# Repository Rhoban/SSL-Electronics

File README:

> Copyright (C) 2019  Adrien Boussicault <adrien.boussicault@labri.fr>
>
> This program is free software: you can redistribute it and/or
> modify it under the terms of the GNU Lesser General Public
> License as published by the Free Software Foundation, either
> version 3 of the License, or (at your option) any later version.
>
> This program is distributed in the hope that it will be useful,
> but WITHOUT ANY WARRANTY; without even the implied warranty of
> MERCHANTABILITY or FITNESS FOR A PARTICULAR PURPOSE.  See the GNU
> Lesser General Public License for more details.
>
> You should have received a copy of the GNU Lesser General Public
> License along with this program.  If not, see
> <http://www.gnu.org/licenses/>.

##################
# Installation : #
##################

Install the following package :

sudo apt-get install dfu-util cu build-essential

Uninstall the modemmanager : 

sudo apt-get remove modemmanager

( The modmeManger will grab the serial line of the USB : /dev/ttyACM0;
if you are using this service, you should prefer do desactivate them with the
following command : systemctl stop ModemManager.service )

Add Udev permition to have access to /dev/ttyACMO

sudo adduser USER plugdev
sudo adduser USER dialout

Add/edit the file /etc/udev/rules.d/42-cycloide.rules and add the following 
lines :

ATTRS{idProduct}=="4567", ATTRS{idVendor}=="f123", MODE="664", GROUP="plugdev" SYMLINK+="brushless"
ATTRS{idProduct}=="5740", ATTRS{idVendor}=="0483", MODE="664", GROUP="plugdev" SYMLINK+="stm32"

The first line is for the normal mode. It allow to comunicate with the 
brushless. The second one is used to flash the firmware.

Restart the udev service :
 
sudo /etc/init.d/udev restart

Download the last ARM compilator from the website :

https://developer.arm.com/tools-and-software/open-source-software/developer-tools/gnu-toolchain/gnu-rm/downloads

And install the compilator in a chosen ARM_DIRECTORY directory.

OPTIONAL INSTALLATION :

You can install JLink tools in order to use JTAG to flash or print.
Go to the website :  

#########################################
# Compile the application               #
#########################################

Jute type

make GCC_PATH=<ARM_DIRECTORY>/bin

###################
# Flash the board #
###################

Three solution are possible dependong of the situation.
IF THE BOARD HAVE NOT YET BEEN FLASHED, YOU SHOULD USE SOLUTION 1) OR 2).
Solution 3) is the most simple one and it is used to update the firmware (we 
need the board to be yet flashed).

Short description of the 3 solutions : 
 1) FLASH BY USB USING THE RESET AND BOOT0 BUTTONS
   This solution doesn't need the board to be yet flashed.
   This solution need USB wire and and an access to the BOOT0 and RESET buttons
   of the board
 2) FLASH BY JTAG USING THE JLink SOFWTARE
   This solution doesn't need the board to be yet flashed.
   This solution need an USB wire (for the power) and a JTAG for the connection.
   This solution Use JLink software (see Optional installation)
   The JLink software download just the part of the memory that have changed.
   So the flash operation are fast and the life of the flash memory is 
   increased.
 3) FLASH BY USB WITHOUT USING THE RESET BUTTONS
   This solution need the board to be yet flashed
   ( by using 1) or  2) ).
   This solution just need a USB wire ! :)
   This solution DO NOT require an acess to the BOOT0 and RESET button ! :)

1) FLASH BY USB USING THE RESET AND BOOT0 BUTTONS

 Connect the USB wire.

 Press and hold the BOOT0 button, then press and realease de RESET button,
 and finally release the BOOT0 button.

 Type the command :
 ./first_flash_with_usb_and_reset_button.sh

2) FLASH BY JTAG USING THE JLink SOFWTARE

 ./jtag_flash.sh

3) FLASH BY USB WITHOUT THE RESET BUTTONS

 ./usb_flash.sh

########################
# Connect to the board #
########################

First Connect the USB wire.

Execute the command 

dmesg

to know on which device the board is connected (usualy it is /dev/ttyACM0).

Open a command line into the board by typing:

cu -l /dev/ttyACM0

Enjoy :) 
(In the command line, help is the first helpfull command to know)

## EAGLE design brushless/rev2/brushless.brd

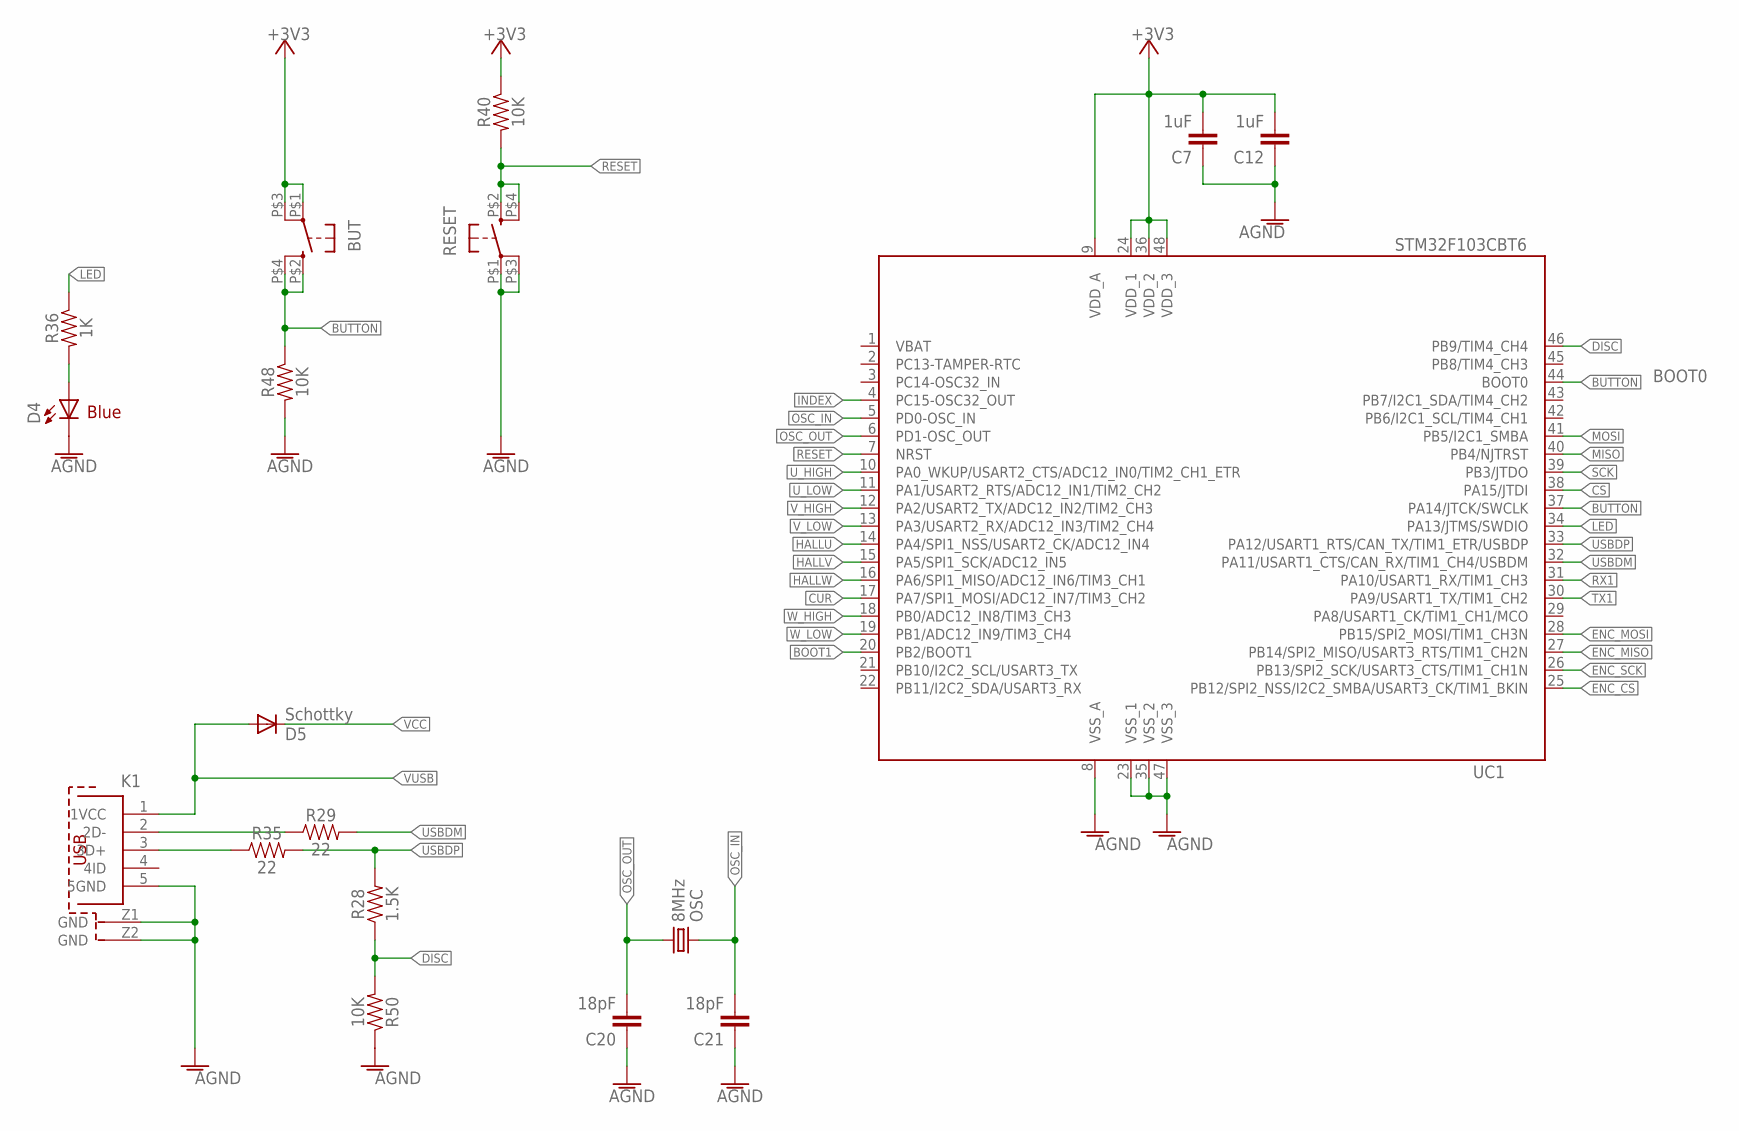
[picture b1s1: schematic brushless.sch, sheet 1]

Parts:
BUT: KMR211GLFS; PUSHBUTTON-KMR241GLFS; FARNELL 1437637
C7, C12: 1uF; 0805@1; FARNELL 2496946
C20, C21: 18pF; 0805@1; FARNELL 1414620
D4: Blue; LED-1206; FARNELL 1581233
D5: Schottky; SOD-323; FARNELL 8734593
K1: 614105150721; FARNELL 2470821
OSC: 8MHz; CRYSTAL-SMD-5X3; FARNELL 2467818
R28: 1.5K; 0805; FARNELL 2446909
R29, R35: 22; 0805; FARNELL 2446926
R36: 1K; 0805; FARNELL 2446904
R40, R48, R50: 10K; 0805; FARNELL 2447553
RESET: KMR211GLFS; PUSHBUTTON-KMR241GLFS; FARNELL 1437637
UC1: STM32F103CBT6; STM32_LQFP48; FARNELL 1606327

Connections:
+3V3: BUT.P$1 (1), BUT.P$3 (3), C7.2, C12.2, R40.1, UC1.9 (VDD_A), UC1.24 (VDD_1), UC1.36 (VDD_2), UC1.48 (VDD_3); also elsewhere on the board
AGND: C7.1, C12.1, C20.1, C21.1, D4.C, K1.5 (5GND), K1.Z1 (GND), K1.Z2 (GND), R48.2, R50.1, RESET.P$1 (1), RESET.P$3 (3), UC1.8 (VSS_A), UC1.23 (VSS_1), UC1.35 (VSS_2), UC1.47 (VSS_3); also elsewhere on the board
BOOT1: UC1.20 (PB2/BOOT1)
BUTTON: BUT.P$2 (2), BUT.P$4 (4), R48.1, UC1.37 (PA14/JTCK/SWCLK), UC1.44 (BOOT0)
CS: UC1.38 (PA15/JTDI); also elsewhere on the board
CUR: UC1.17 (PA7/SPI1_MOSI/ADC12_IN7/TIM3_CH2); also elsewhere on the board
DISC: R28.1, R50.2, UC1.46 (PB9/TIM4_CH4)
ENC_CS: UC1.25 (PB12/SPI2_NSS/I2C2_SMBA/USART3_CK/TIM1_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); also elsewhere on the board
ENC_MISO: UC1.27 (PB14/SPI2_MISO/USART3_RTS/TIM1_CH2N); also elsewhere on the board
ENC_MOSI: UC1.28 (PB15/SPI2_MOSI/TIM1_CH3N); also elsewhere on the board
ENC_SCK: UC1.26 (PB13/SPI2_SCK/USART3_CTS/TIM1_CH1N); also elsewhere on the board
HALLU: UC1.14 (PA4/SPI1_NSS/USART2_CK/ADC12_IN4); also elsewhere on the board
HALLV: UC1.15 (PA5/SPI1_SCK/ADC12_IN5); also elsewhere on the board
HALLW: UC1.16 (PA6/SPI1_MISO/ADC12_IN6/TIM3_CH1); also elsewhere on the board
INDEX: UC1.4 (PC15-OSC32_OUT)
LED: R36.1, UC1.34 (PA13/JTMS/SWDIO)
MISO: UC1.40 (PB4/NJTRST); also elsewhere on the board
MOSI: UC1.41 (PB5/I2C1_SMBA); also elsewhere on the board
unnamed: D4.A, R36.2
unnamed: K1.2 (2D-), R29.1
unnamed: K1.3 (3D+), R35.1
OSC_IN: C21.2, OSC.3 (2), UC1.5 (PD0-OSC_IN)
OSC_OUT: C20.2, OSC.1, UC1.6 (PD1-OSC_OUT)
RESET: R40.2, RESET.P$2 (2), RESET.P$4 (4), UC1.7 (NRST)
RX1: UC1.31 (PA10/USART1_RX/TIM1_CH3)
SCK: UC1.39 (PB3/JTDO); also elsewhere on the board
TX1: UC1.30 (PA9/USART1_TX/TIM1_CH2)
USBDM: R29.2, UC1.32 (PA11/USART1_CTS/CAN_RX/TIM1_CH4/USBDM)
USBDP: R28.2, R35.2, UC1.33 (PA12/USART1_RTS/CAN_TX/TIM1_ETR/USBDP)
U_HIGH: UC1.10 (PA0_WKUP/USART2_CTS/ADC12_IN0/TIM2_CH1_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); also elsewhere on the board
U_LOW: UC1.11 (PA1/USART2_RTS/ADC12_IN1/TIM2_CH2); also elsewhere on the board
VBAT: UC1.1 (VBAT)
VCC: D5.1 (C); also elsewhere on the board
VUSB: D5.2 (A), K1.1 (1VCC); also elsewhere on the board
V_HIGH: UC1.12 (PA2/USART2_TX/ADC12_IN2/TIM2_CH3); also elsewhere on the board
V_LOW: UC1.13 (PA3/USART2_RX/ADC12_IN3/TIM2_CH4); also elsewhere on the board
W_HIGH: UC1.18 (PB0/ADC12_IN8/TIM3_CH3); also elsewhere on the board
W_LOW: UC1.19 (PB1/ADC12_IN9/TIM3_CH4); also elsewhere on the board

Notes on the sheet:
BOOT0
Blue

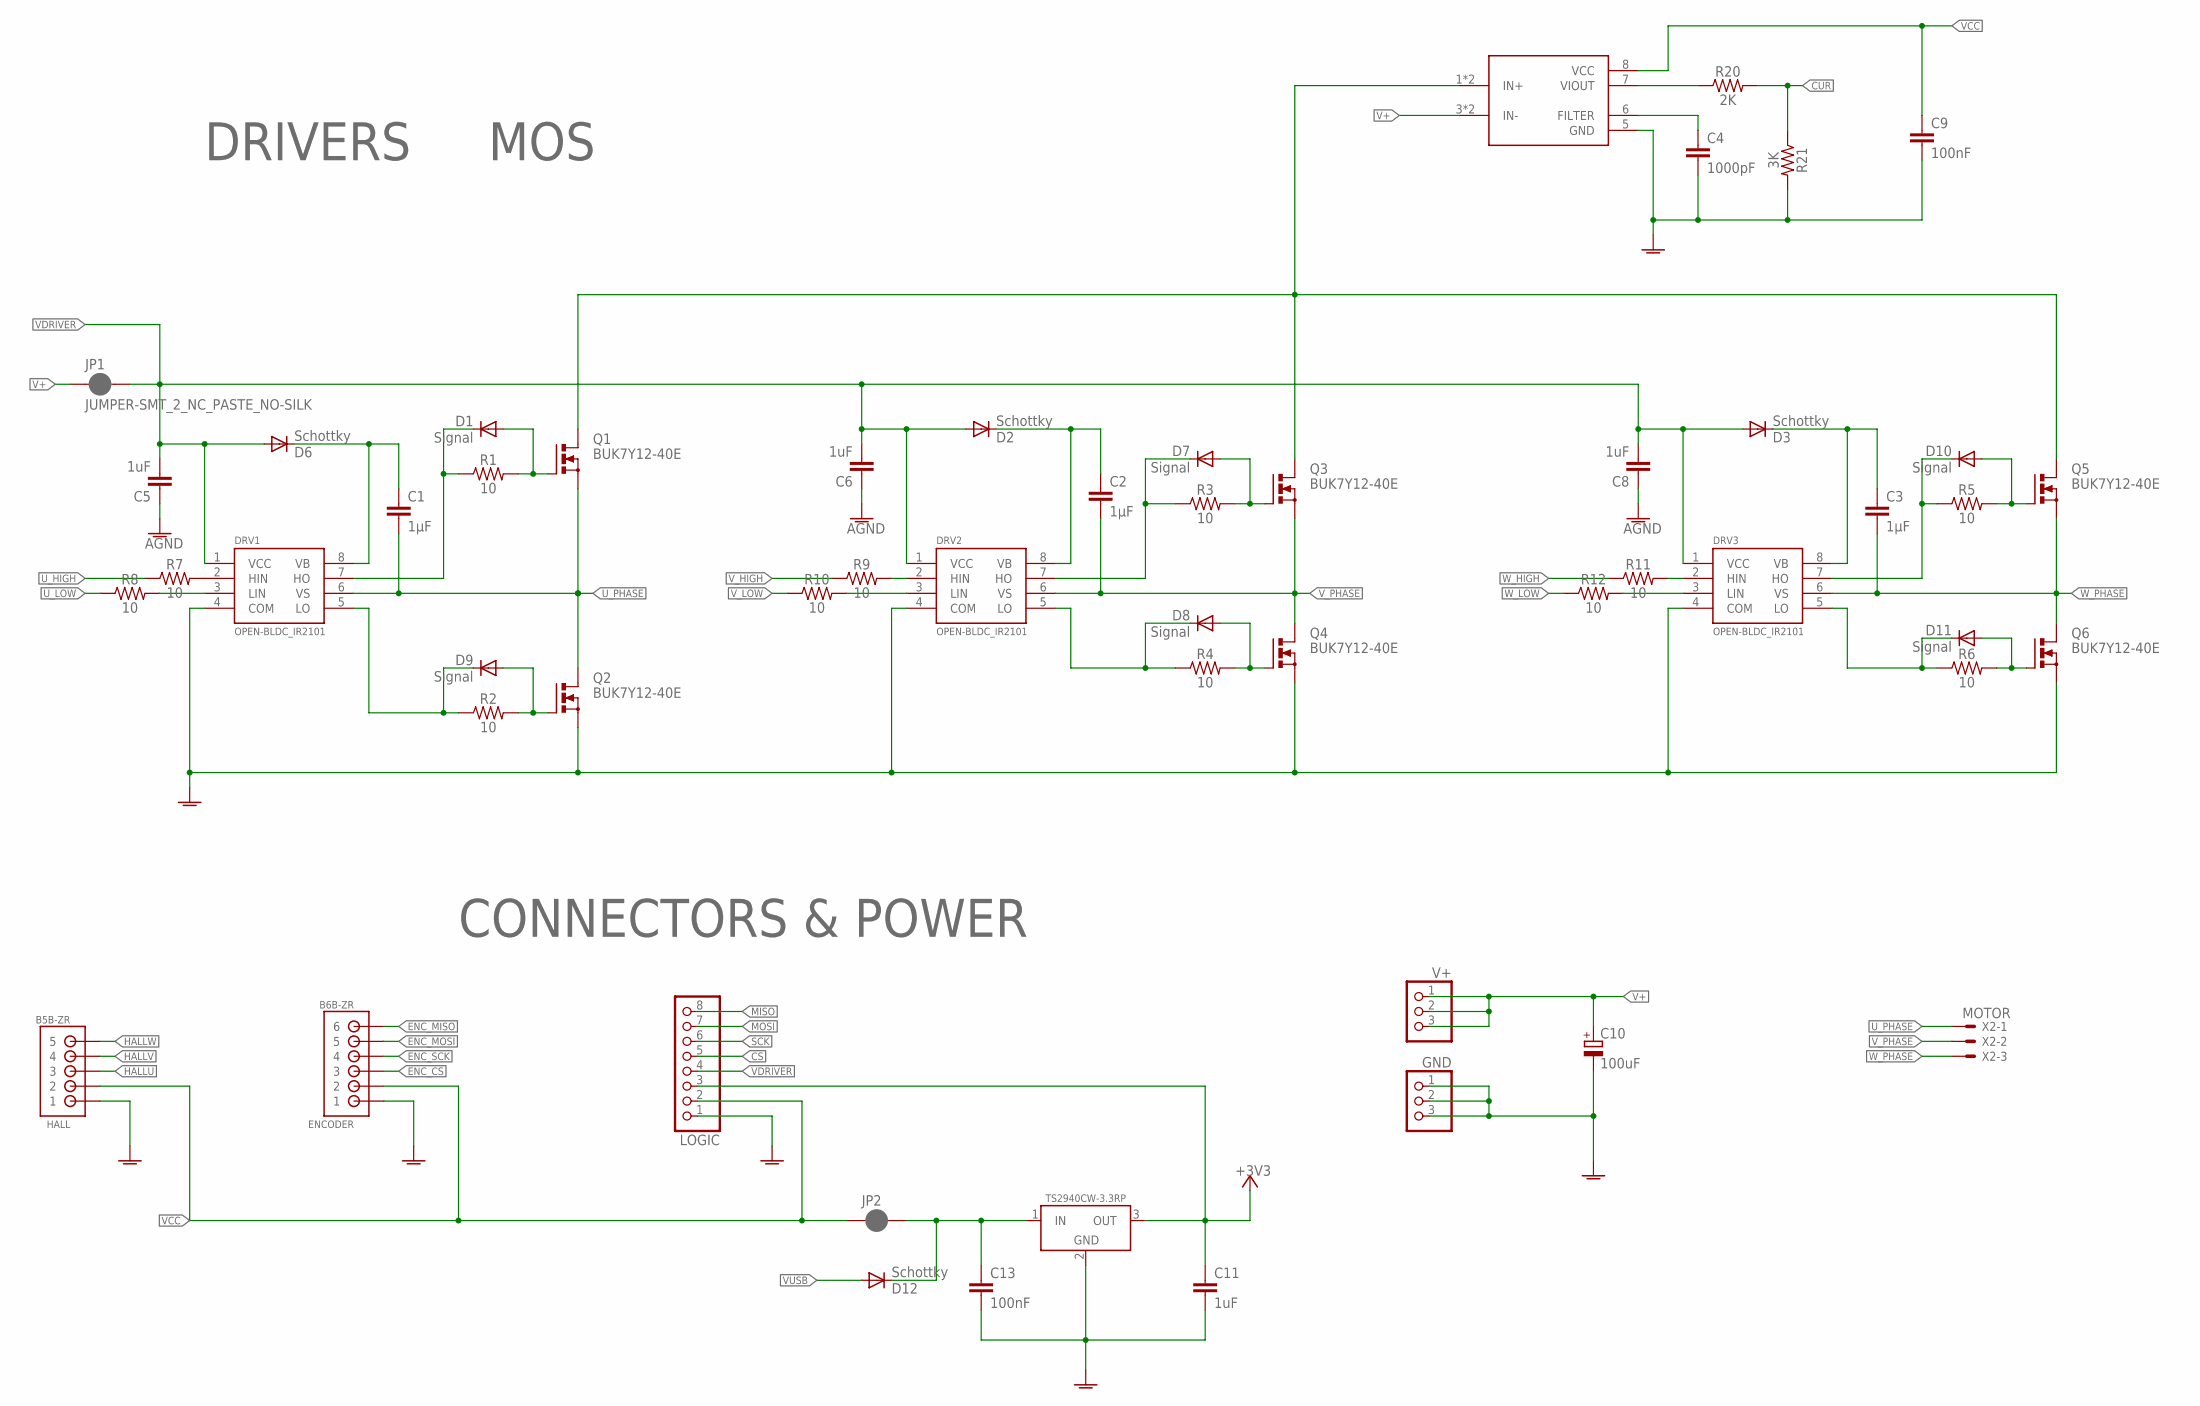
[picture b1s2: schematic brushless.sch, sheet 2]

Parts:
C1, C2, C3: 1µF; 0805; FARNELL 2496946
C4: 1000pF; 0805@1; FARNELL 2392334
C5, C6, C8, C11: 1uF; 0805@1; FARNELL 2496946
C9, C13: 100nF; 0805@1; FARNELL 1759143RL
C10: 100uF; E3,5-8; FARNELL 1870964
D1, D7, D8, D9, D10, D11: Signal; SOD-323; FARNELL 1843678RL
D2, D3, D6, D12: Schottky; SOD-323; FARNELL 8734593
DRV1, DRV2, DRV3: OPEN-BLDC_IR2101; OPEN-BLDC_SO-8; FARNELL 8638756
ENCODER: B6B-ZR
GND: CONNEC_1X03; FARNELL 1022248
HALL: B5B-ZR
JP1, JP2: JUMPER-SMT_2_NC_PASTE_NO-SILK; SMT-JUMPER_2_NC_PASTE_NO-SILK
LOGIC: CONNEC_1X08; FARNELL 1022256
Q1, Q2, Q3, Q4, Q5, Q6: BUK7Y12-40E; SOT669; FARNELL 2319916
R1, R2, R3, R4, R5, R6, R7, R8, R9, R10, R11, R12: 10; 0805; FARNELL 2498048
R20: 2K; 0805; FARNELL 2446939
R21: 3K; 0805; FARNELL 2446965
REG1: TS2940CW-3.3RP; SOT223; FARNELL 7261403
SENSE: ACS712; SO8; FARNELL 1329624
V+: CONNEC_1X03; FARNELL 1022248
X2: MOTOR; JST-XH-03-PACKAGE-LONG-PAD

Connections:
+3V3: C11.1, LOGIC.3, REG1.3 (OUT); also elsewhere on the board
AGND: C4.2, C5.1, C6.1, C8.1, C9.2, C10.-, C11.2, C13.2, DRV1.4 (COM), DRV2.4 (COM), DRV3.4 (COM), ENCODER.1, GND.1, GND.2, GND.3, HALL.1, LOGIC.1, Q2.1 (S), Q2.2 (S), Q2.3 (S), Q4.1 (S), Q4.2 (S), Q4.3 (S), Q6.1 (S), Q6.2 (S), Q6.3 (S), R21.2, REG1.2 (GND), SENSE.5 (GND); also elsewhere on the board
CS: LOGIC.5; also elsewhere on the board
CUR: R20.2, R21.1; also elsewhere on the board
ENC_CS: ENCODER.3; also elsewhere on the board
ENC_MISO: ENCODER.6; also elsewhere on the board
ENC_MOSI: ENCODER.5; also elsewhere on the board
ENC_SCK: ENCODER.4; also elsewhere on the board
HALLU: HALL.3; also elsewhere on the board
HALLV: HALL.4; also elsewhere on the board
HALLW: HALL.5; also elsewhere on the board
MISO: LOGIC.8; also elsewhere on the board
MOSI: LOGIC.7; also elsewhere on the board
unnamed: D7.2 (A), Q3.4 (G), R3.2
unnamed: D9.2 (A), Q2.4 (G), R2.2
unnamed: DRV1.2 (HIN), R7.2
unnamed: C1.1, D6.1 (C), DRV1.8 (VB)
unnamed: D8.2 (A), Q4.4 (G), R4.2
unnamed: D10.2 (A), Q5.4 (G), R5.2
unnamed: DRV1.3 (LIN), R8.2
unnamed: D11.2 (A), Q6.4 (G), R6.2
unnamed: C2.1, D2.1 (C), DRV2.8 (VB)
unnamed: D1.2 (A), Q1.4 (G), R1.2
unnamed: D10.1 (C), DRV3.7 (HO), R5.1
unnamed: D11.1 (C), DRV3.5 (LO), R6.1
unnamed: DRV2.3 (LIN), R10.2
unnamed: C3.1, D3.1 (C), DRV3.8 (VB)
unnamed: DRV2.2 (HIN), R9.2
unnamed: DRV3.2 (HIN), R11.2
unnamed: DRV3.3 (LIN), R12.2
unnamed: C13.1, D12.1 (C), JP2.2, REG1.1 (IN)
unnamed: R20.1, SENSE.7 (VIOUT)
unnamed: C4.1, SENSE.6 (FILTER)
SCK: LOGIC.6; also elsewhere on the board
U_GATE_HIGH: D1.1 (C), DRV1.7 (HO), R1.1
U_GATE_LOW: D9.1 (C), DRV1.5 (LO), R2.1
U_HIGH: R7.1; also elsewhere on the board
U_LOW: R8.1; also elsewhere on the board
U_PHASE: C1.2, DRV1.6 (VS), Q1.1 (S), Q1.2 (S), Q1.3 (S), Q2.MB (D), X2.1
V+: C10.+, JP1.1, SENSE.3 (IN-), SENSE.4 (IN-), V+.1, V+.2, V+.3
V+_MOS: Q1.MB (D), Q3.MB (D), Q5.MB (D), SENSE.1 (IN+), SENSE.2 (IN+)
VCC: C9.1, ENCODER.2, HALL.2, JP2.1, LOGIC.2, SENSE.8 (VCC); also elsewhere on the board
VDRIVER: C5.2, C6.2, C8.2, D2.2 (A), D3.2 (A), D6.2 (A), DRV1.1 (VCC), DRV2.1 (VCC), DRV3.1 (VCC), JP1.2, LOGIC.4
VUSB: D12.2 (A); also elsewhere on the board
V_GATE_HIGH: D7.1 (C), DRV2.7 (HO), R3.1
V_GATE_LOW: D8.1 (C), DRV2.5 (LO), R4.1
V_HIGH: R9.1; also elsewhere on the board
V_LOW: R10.1; also elsewhere on the board
V_PHASE: C2.2, DRV2.6 (VS), Q3.1 (S), Q3.2 (S), Q3.3 (S), Q4.MB (D), X2.2
W_HIGH: R11.1; also elsewhere on the board
W_LOW: R12.1; also elsewhere on the board
W_PHASE: C3.2, DRV3.6 (VS), Q5.1 (S), Q5.2 (S), Q5.3 (S), Q6.MB (D), X2.3

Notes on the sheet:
MOS
DRIVERS
CONNECTORS & POWER

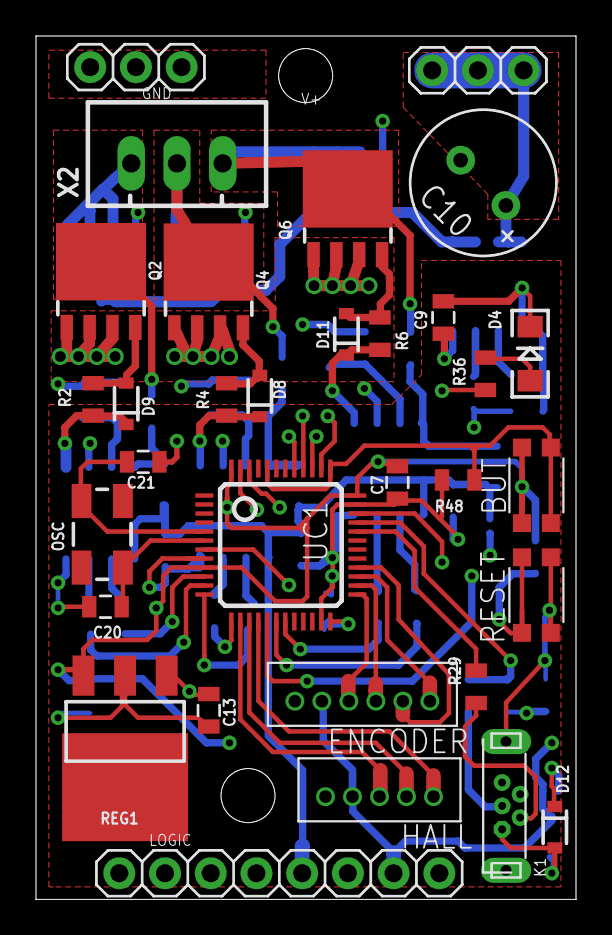
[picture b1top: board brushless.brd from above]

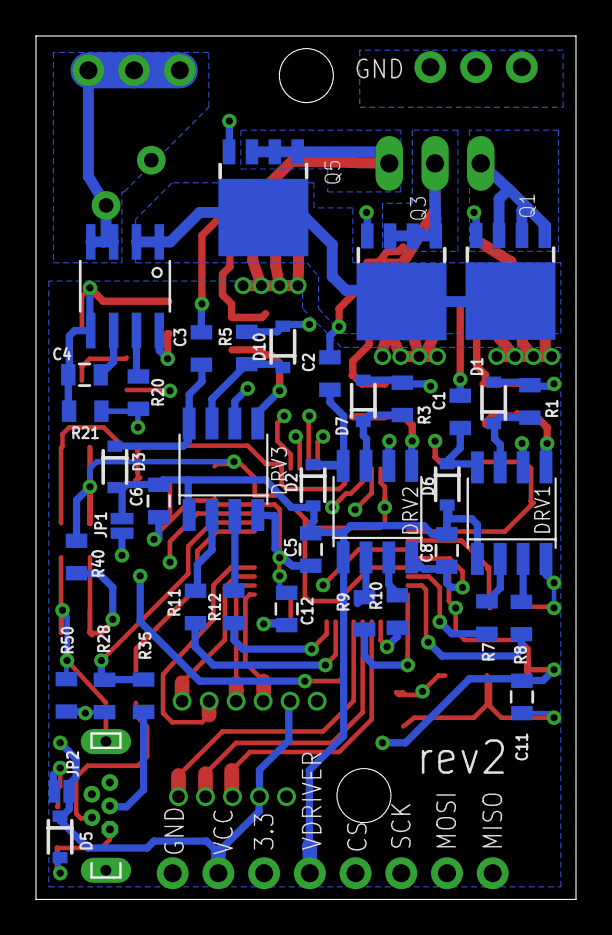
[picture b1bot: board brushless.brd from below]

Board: 4 copper layers, 30.0 x 48.0 mm, 72 parts (40 on the bottom side), 63 nets.

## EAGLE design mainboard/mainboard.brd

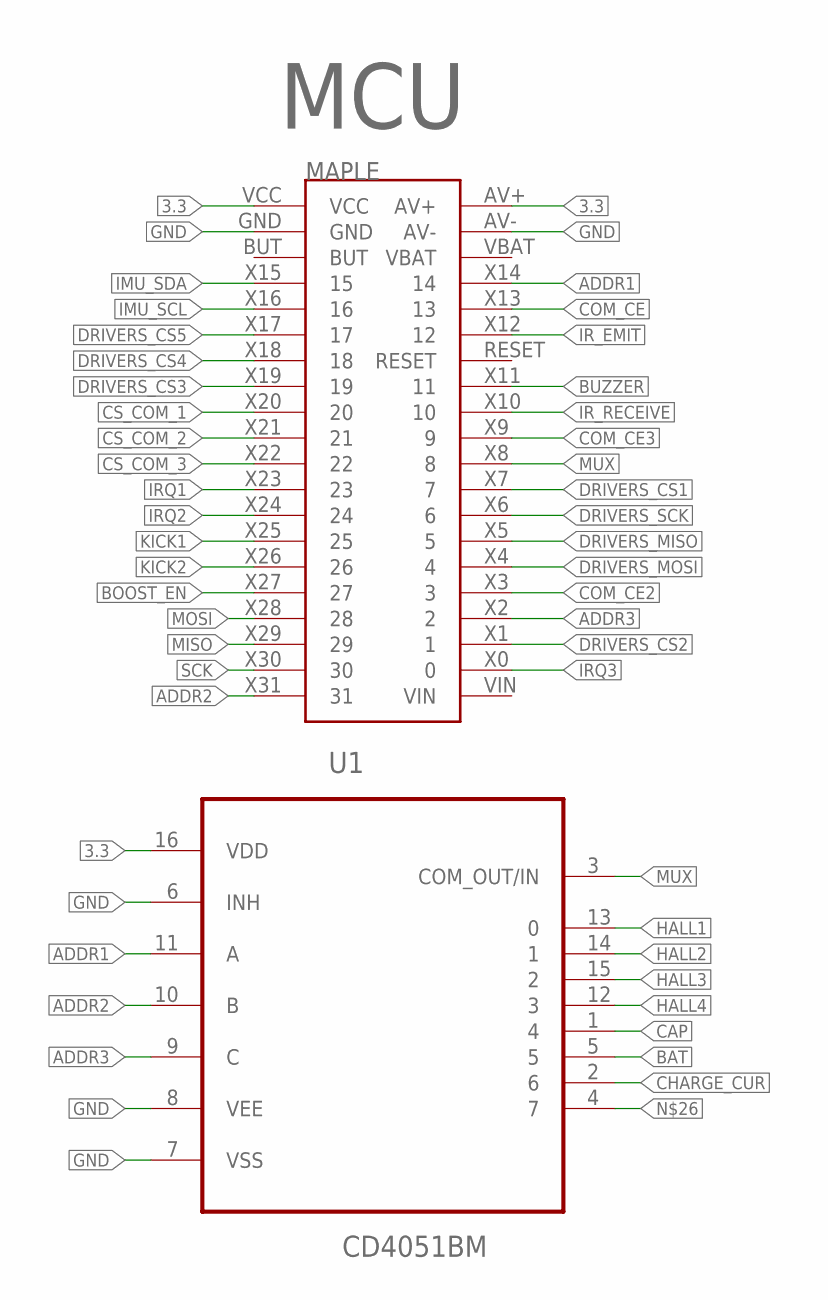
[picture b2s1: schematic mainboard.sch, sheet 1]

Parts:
MAPLE: MAPLE_MINI; CONNEC_2X20; FARNELL 1593469,1593469
U1: CD4051BM; SOIC127P600X175-16N; FARNELL 2334931

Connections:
3.3: MAPLE.AV+, MAPLE.VCC, U1.16 (VDD); also elsewhere on the board
ADDR1: MAPLE.X14 (14), U1.11 (A)
ADDR2: MAPLE.X31 (31), U1.10 (B)
ADDR3: MAPLE.X2 (2), U1.9 (C)
BAT: U1.5; also elsewhere on the board
BOOST_EN: MAPLE.X27 (27); also elsewhere on the board
BUZZER: MAPLE.X11 (11); also elsewhere on the board
CAP: U1.1 (4); also elsewhere on the board
CHARGE_CUR: U1.2 (6); also elsewhere on the board
COM_CE: MAPLE.X13 (13)
COM_CE2: MAPLE.X3 (3); also elsewhere on the board
COM_CE3: MAPLE.X9 (9); also elsewhere on the board
CS_COM_1: MAPLE.X20 (20); also elsewhere on the board
CS_COM_2: MAPLE.X21 (21); also elsewhere on the board
CS_COM_3: MAPLE.X22 (22); also elsewhere on the board
DRIVERS_CS1: MAPLE.X7 (7); also elsewhere on the board
DRIVERS_CS2: MAPLE.X1 (1); also elsewhere on the board
DRIVERS_CS3: MAPLE.X19 (19); also elsewhere on the board
DRIVERS_CS4: MAPLE.X18 (18); also elsewhere on the board
DRIVERS_CS5: MAPLE.X17 (17); also elsewhere on the board
DRIVERS_MISO: MAPLE.X5 (5); also elsewhere on the board
DRIVERS_MOSI: MAPLE.X4 (4); also elsewhere on the board
DRIVERS_SCK: MAPLE.X6 (6); also elsewhere on the board
GND: MAPLE.AV-, MAPLE.GND, U1.6 (INH), U1.7 (VSS), U1.8 (VEE); also elsewhere on the board
HALL1: U1.13 (0); also elsewhere on the board
HALL2: U1.14 (1); also elsewhere on the board
HALL3: U1.15 (2); also elsewhere on the board
HALL4: U1.12 (3); also elsewhere on the board
IMU_SCL: MAPLE.X16 (16); also elsewhere on the board
IMU_SDA: MAPLE.X15 (15); also elsewhere on the board
IRQ1: MAPLE.X23 (23); also elsewhere on the board
IRQ2: MAPLE.X24 (24); also elsewhere on the board
IRQ3: MAPLE.X0 (0); also elsewhere on the board
IR_EMIT: MAPLE.X12 (12); also elsewhere on the board
IR_RECEIVE: MAPLE.X10 (10); also elsewhere on the board
KICK1: MAPLE.X25 (25); also elsewhere on the board
KICK2: MAPLE.X26 (26); also elsewhere on the board
MISO: MAPLE.X29 (29); also elsewhere on the board
MOSI: MAPLE.X28 (28); also elsewhere on the board
MUX: MAPLE.X8 (8), U1.3 (COM_OUT/IN)
SCK: MAPLE.X30 (30); also elsewhere on the board

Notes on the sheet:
MCU

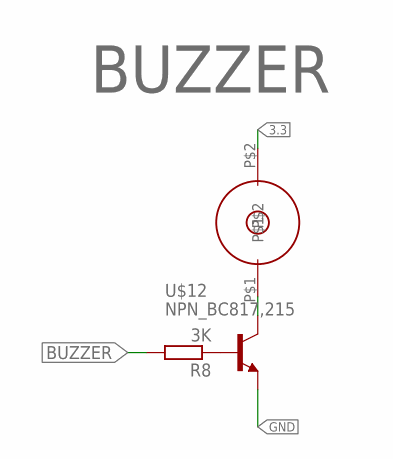
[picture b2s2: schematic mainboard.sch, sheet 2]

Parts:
R8: 3K; R0805; FARNELL 2446965
U$12: NPN_BC817,215; SOT-23; FARNELL 1081223
U$13: BUZZER66

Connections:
3.3: U$13.P$2; also elsewhere on the board
BUZZER: R8.2; also elsewhere on the board
GND: U$12.2 (E); also elsewhere on the board
unnamed: R8.1, U$12.1 (B)
unnamed: U$12.3 (C), U$13.P$1

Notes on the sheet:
BUZZER

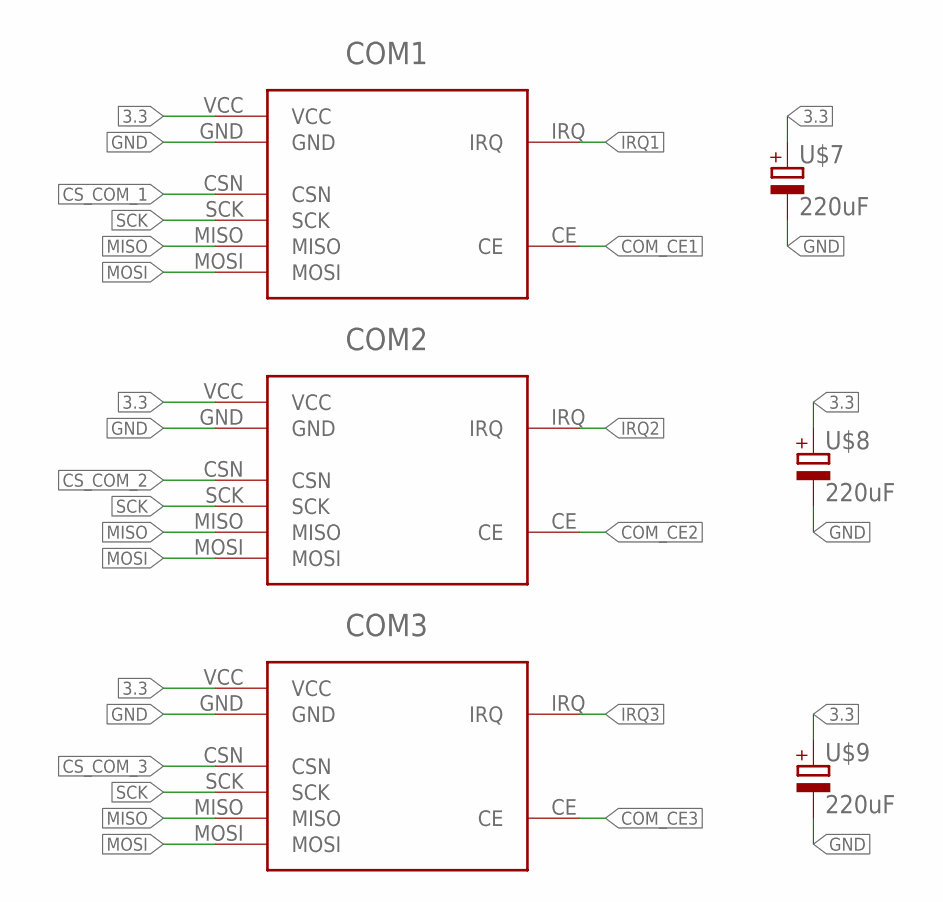
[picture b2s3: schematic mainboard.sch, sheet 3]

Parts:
COM1, COM2, COM3: NRF24L01; FARNELL 1668343
U$7, U$8, U$9: 220uF; PANASONIC_D8; FARNELL 1850103

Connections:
3.3: COM1.VCC, COM2.VCC, COM3.VCC, U$7.+, U$8.+, U$9.+; also elsewhere on the board
COM_CE1: COM1.CE
COM_CE2: COM2.CE; also elsewhere on the board
COM_CE3: COM3.CE; also elsewhere on the board
CS_COM_1: COM1.CSN; also elsewhere on the board
CS_COM_2: COM2.CSN; also elsewhere on the board
CS_COM_3: COM3.CSN; also elsewhere on the board
GND: COM1.GND, COM2.GND, COM3.GND, U$7.-, U$8.-, U$9.-; also elsewhere on the board
IRQ1: COM1.IRQ; also elsewhere on the board
IRQ2: COM2.IRQ; also elsewhere on the board
IRQ3: COM3.IRQ; also elsewhere on the board
MISO: COM1.MISO, COM2.MISO, COM3.MISO; also elsewhere on the board
MOSI: COM1.MOSI, COM2.MOSI, COM3.MOSI; also elsewhere on the board
SCK: COM1.SCK, COM2.SCK, COM3.SCK; also elsewhere on the board

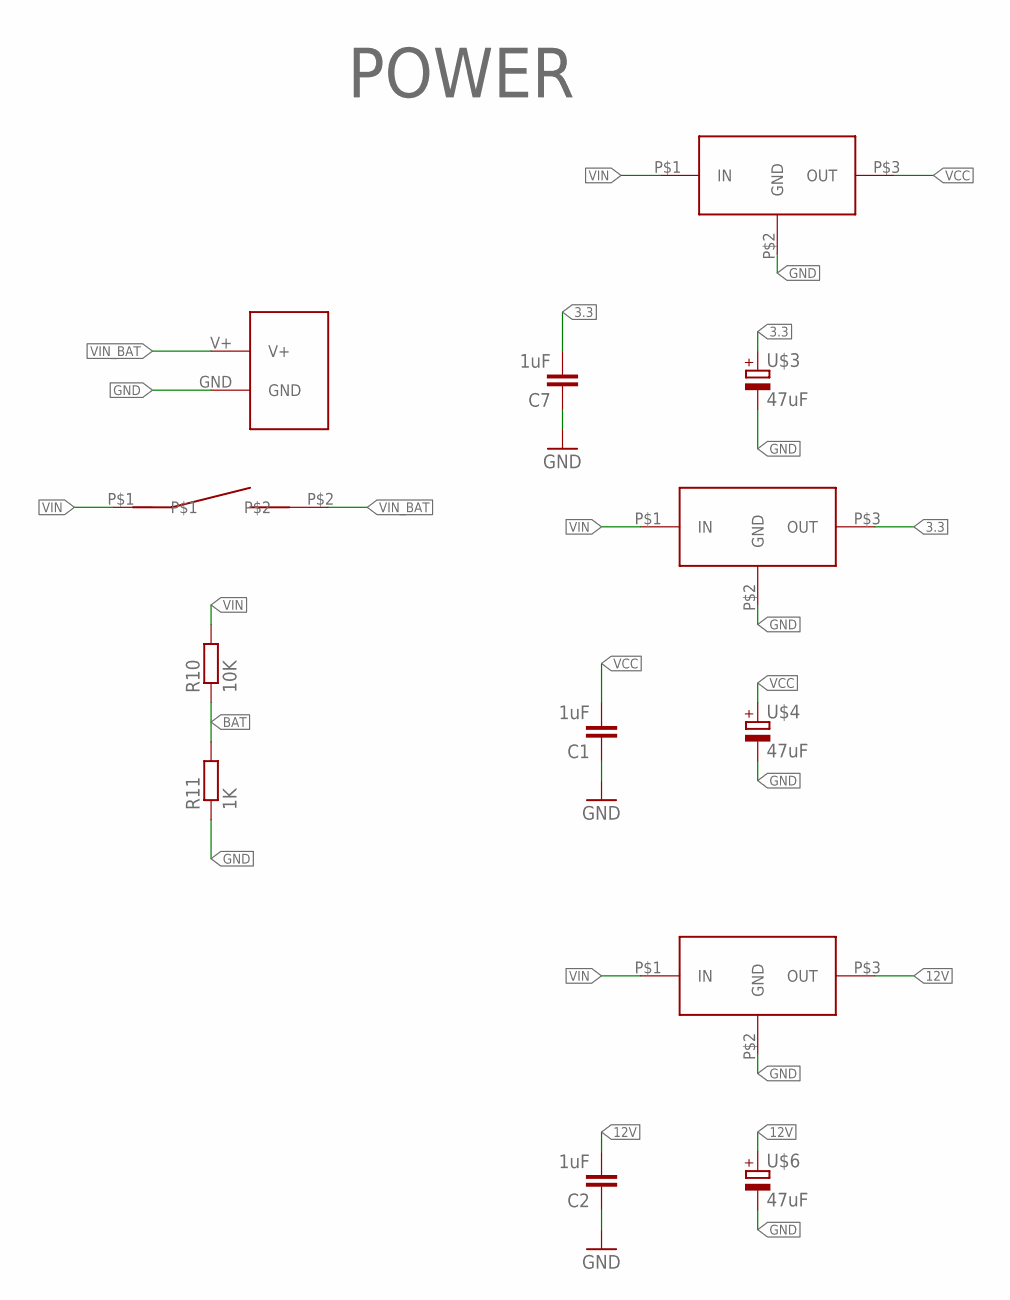
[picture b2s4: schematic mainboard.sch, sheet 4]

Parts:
C1, C2, C7: 1uF; 0805@1; FARNELL 2496946
R10: 10K; R0805; FARNELL 2447553
R11: 1K; R0805; FARNELL 2446904
REG3.3V: REG_5V; TRACOPOWER; FARNELL 1696319
REG3.3V1: REG_5V; TRACOPOWER; FARNELL 1672130
REG5V: REG_5V; TRACOPOWER; FARNELL 1696320
U$3, U$4, U$6: 47uF; PANASONIC_D; FARNELL 9696946
U$15: SRB22A2FBBNN; FARNELL 1383947
XT60: CONNEC_ALIM; XT60

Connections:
3.3: C7.2, REG3.3V.P$3 (OUT), U$3.+; also elsewhere on the board
12V: C2.2, REG3.3V1.P$3 (OUT), U$6.+; also elsewhere on the board
BAT: R10.1, R11.2; also elsewhere on the board
GND: C1.1, C2.1, C7.1, R11.1, REG3.3V.P$2 (GND), REG3.3V1.P$2 (GND), REG5V.P$2 (GND), U$3.-, U$4.-, U$6.-, XT60.GND; also elsewhere on the board
VCC: C1.2, REG5V.P$3 (OUT), U$4.+; also elsewhere on the board
VIN: R10.2, REG3.3V.P$1 (IN), REG3.3V1.P$1 (IN), REG5V.P$1 (IN), U$15.P$1; also elsewhere on the board
VIN_BAT: U$15.P$2, XT60.V+

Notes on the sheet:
POWER

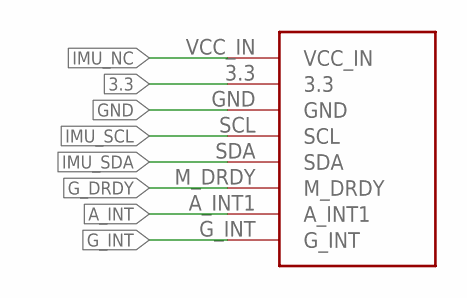
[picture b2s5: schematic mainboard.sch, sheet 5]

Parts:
U$2: GY-85; FARNELL 1593463

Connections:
3.3: U$2.3.3; also elsewhere on the board
A_INT: U$2.A_INT1
GND: U$2.GND; also elsewhere on the board
G_DRDY: U$2.M_DRDY
G_INT: U$2.G_INT
IMU_NC: U$2.VCC_IN
IMU_SCL: U$2.SCL; also elsewhere on the board
IMU_SDA: U$2.SDA; also elsewhere on the board

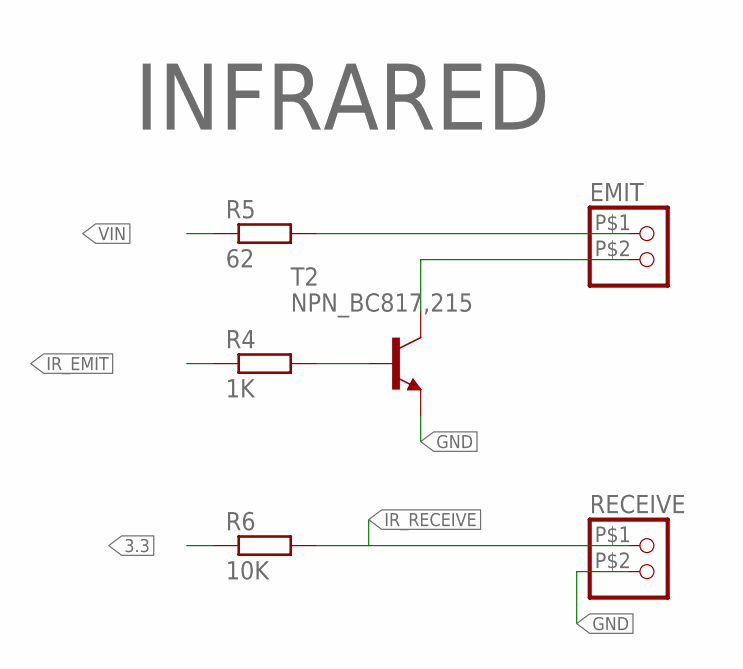
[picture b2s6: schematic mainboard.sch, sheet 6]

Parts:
EMIT: CONNEC_1X02JST-ZH; JST_ZH_2P; FARNELL 1212763
R4: 1K; R0805; FARNELL 2446904
R5: 62; R0805; FARNELL 2138819
R6: 10K; R0805; FARNELL 2447553
RECEIVE: CONNEC_1X02JST-ZH; JST_ZH_2P; FARNELL 3152856
T2: NPN_BC817,215; SOT-23; FARNELL 1081223

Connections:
3.3: R6.1; also elsewhere on the board
GND: RECEIVE.P$2 (2), T2.2 (E); also elsewhere on the board
IR_EMIT: R4.1; also elsewhere on the board
IR_RECEIVE: R6.2, RECEIVE.P$1 (1); also elsewhere on the board
unnamed: EMIT.P$1 (1), R5.2
unnamed: EMIT.P$2 (2), T2.3 (C)
unnamed: R4.2, T2.1 (B)
VIN: R5.1; also elsewhere on the board

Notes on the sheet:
INFRARED

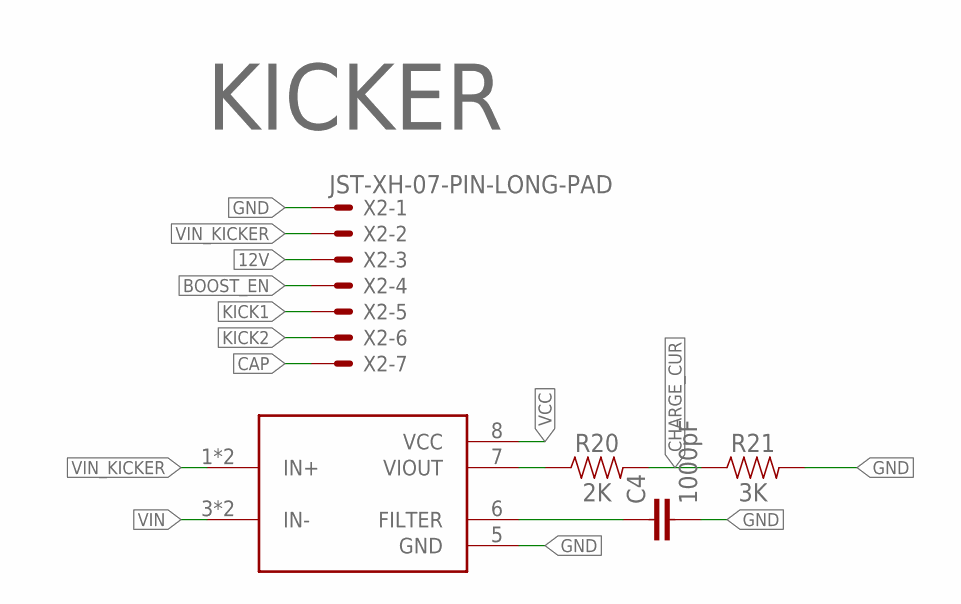
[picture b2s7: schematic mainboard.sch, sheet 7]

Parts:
C4: 1000pF; 0805@1; FARNELL 2496935
R20: 2K; 0805; FARNELL 2446939
R21: 3K; 0805; FARNELL 2446965
SENSE: ACS712; SO8; FARNELL 1329623
X2: JST-XH-07-PIN-LONG-PAD; JST-XH-07-PACKAGE-LONG-PAD

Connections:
12V: X2.3; also elsewhere on the board
BOOST_EN: X2.4; also elsewhere on the board
CAP: X2.7; also elsewhere on the board
CHARGE_CUR: R20.2, R21.1; also elsewhere on the board
GND: C4.2, R21.2, SENSE.5 (GND), X2.1; also elsewhere on the board
KICK1: X2.5; also elsewhere on the board
KICK2: X2.6; also elsewhere on the board
unnamed: R20.1, SENSE.7 (VIOUT)
unnamed: C4.1, SENSE.6 (FILTER)
VCC: SENSE.8 (VCC); also elsewhere on the board
VIN: SENSE.3 (IN-), SENSE.4 (IN-); also elsewhere on the board
VIN_KICKER: SENSE.1 (IN+), SENSE.2 (IN+), X2.2

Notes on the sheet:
KICKER

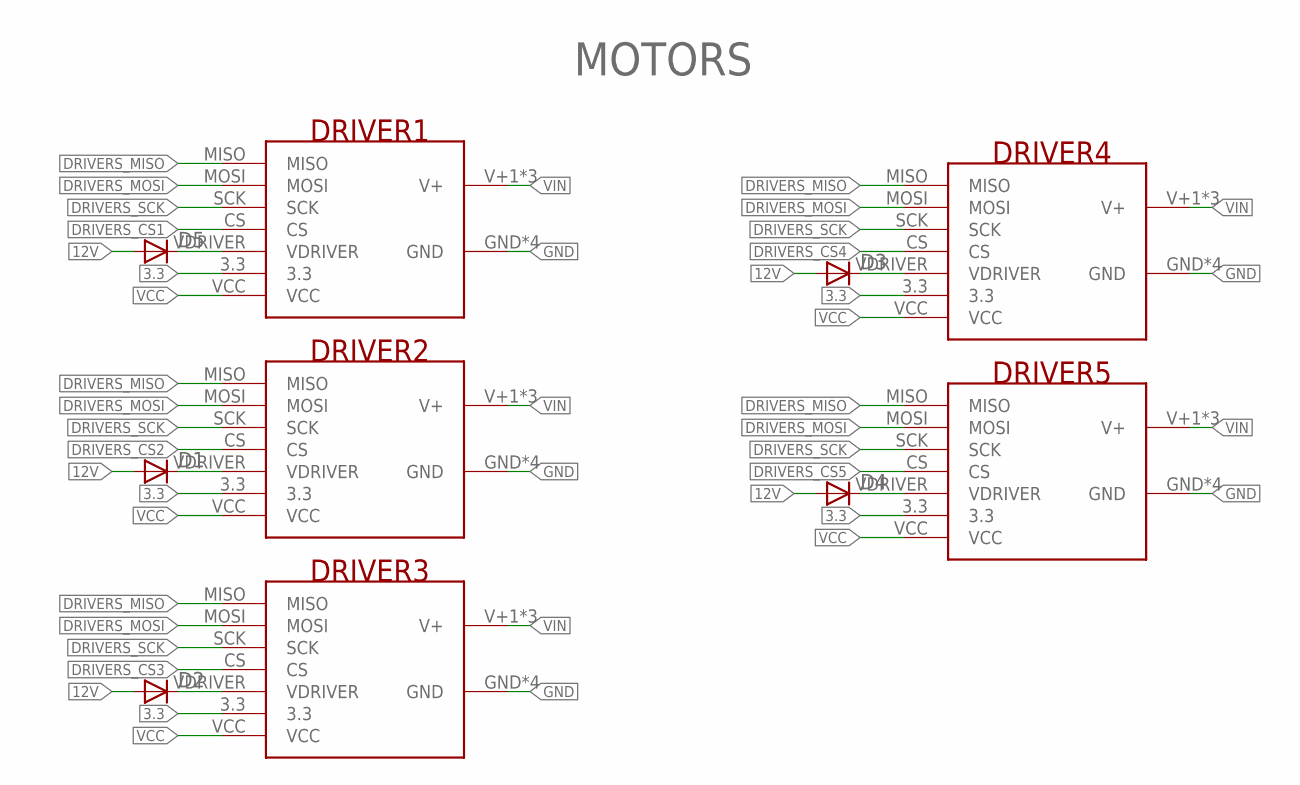
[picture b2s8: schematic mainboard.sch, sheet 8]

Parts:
D1, D2, D3, D4, D5: DIODESOD; SOD-323; FARNELL 8737843RL
DRIVER1, DRIVER2, DRIVER3, DRIVER4, DRIVER5: RHOBAN_BL_DRIVER; FARNELL 1593459,1593459,1593463

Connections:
3.3: DRIVER1.3.3, DRIVER2.3.3, DRIVER3.3.3, DRIVER4.3.3, DRIVER5.3.3; also elsewhere on the board
12V: D1.2 (A), D2.2 (A), D3.2 (A), D4.2 (A), D5.2 (A); also elsewhere on the board
DRIVERS_CS1: DRIVER1.CS; also elsewhere on the board
DRIVERS_CS2: DRIVER2.CS; also elsewhere on the board
DRIVERS_CS3: DRIVER3.CS; also elsewhere on the board
DRIVERS_CS4: DRIVER4.CS; also elsewhere on the board
DRIVERS_CS5: DRIVER5.CS; also elsewhere on the board
DRIVERS_MISO: DRIVER1.MISO, DRIVER2.MISO, DRIVER3.MISO, DRIVER4.MISO, DRIVER5.MISO; also elsewhere on the board
DRIVERS_MOSI: DRIVER1.MOSI, DRIVER2.MOSI, DRIVER3.MOSI, DRIVER4.MOSI, DRIVER5.MOSI; also elsewhere on the board
DRIVERS_SCK: DRIVER1.SCK, DRIVER2.SCK, DRIVER3.SCK, DRIVER4.SCK, DRIVER5.SCK; also elsewhere on the board
GND: DRIVER1.GND, DRIVER1.GND2 (GND), DRIVER1.GND3 (GND), DRIVER1.GND4 (GND), DRIVER2.GND, DRIVER2.GND2 (GND), DRIVER2.GND3 (GND), DRIVER2.GND4 (GND), DRIVER3.GND, DRIVER3.GND2 (GND), DRIVER3.GND3 (GND), DRIVER3.GND4 (GND), DRIVER4.GND, DRIVER4.GND2 (GND), DRIVER4.GND3 (GND), DRIVER4.GND4 (GND), DRIVER5.GND, DRIVER5.GND2 (GND), DRIVER5.GND3 (GND), DRIVER5.GND4 (GND); also elsewhere on the board
unnamed: D5.1 (C), DRIVER1.VDRIVER
unnamed: D3.1 (C), DRIVER4.VDRIVER
unnamed: D4.1 (C), DRIVER5.VDRIVER
unnamed: D2.1 (C), DRIVER3.VDRIVER
unnamed: D1.1 (C), DRIVER2.VDRIVER
VCC: DRIVER1.VCC, DRIVER2.VCC, DRIVER3.VCC, DRIVER4.VCC, DRIVER5.VCC; also elsewhere on the board
VIN: DRIVER1.V+1 (V+), DRIVER1.V+2 (V+), DRIVER1.V+3 (V+), DRIVER2.V+1 (V+), DRIVER2.V+2 (V+), DRIVER2.V+3 (V+), DRIVER3.V+1 (V+), DRIVER3.V+2 (V+), DRIVER3.V+3 (V+), DRIVER4.V+1 (V+), DRIVER4.V+2 (V+), DRIVER4.V+3 (V+), DRIVER5.V+1 (V+), DRIVER5.V+2 (V+), DRIVER5.V+3 (V+); also elsewhere on the board

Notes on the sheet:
MOTORS

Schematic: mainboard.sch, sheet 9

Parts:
R1, R2, R3, R7: 10K; R0805; FARNELL 2447553
U$1, U$5, U$10, U$11: DRV5023FAEDBZRQ1; SOT-23; FARNELL 2673327RL

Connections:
3.3: R1.2, R2.2, R3.2, R7.2, U$1.1 (VCC), U$5.1 (VCC), U$10.1 (VCC), U$11.1 (VCC); also elsewhere on the board
GND: U$1.3 (GND), U$5.3 (GND), U$10.3 (GND), U$11.3 (GND); also elsewhere on the board
HALL1: R1.1, U$1.2 (OUT); also elsewhere on the board
HALL2: R2.1, U$5.2 (OUT); also elsewhere on the board
HALL3: R3.1, U$10.2 (OUT); also elsewhere on the board
HALL4: R7.1, U$11.2 (OUT); also elsewhere on the board

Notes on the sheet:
HALL

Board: 2 copper layers, 58 parts (11 on the bottom side), 57 nets, no tracks yet.

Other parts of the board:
U$14, U$16, U$17, U$18: STAND-OFF

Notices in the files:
parts and their libraries:
SparkFun-Passives: Licensing: CC v3.0 Share-Alike You are welcome to use this library for commercial purposes.
SparkFun-Resistors: Licensing: Creative Commons ShareAlike 4.0 International - https://creativecommons.org/licenses/by-sa/4.0
